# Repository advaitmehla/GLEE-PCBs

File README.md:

# GLEE-PCBs

This repository is for the schematics and PCBs I've worked on for Satlab.

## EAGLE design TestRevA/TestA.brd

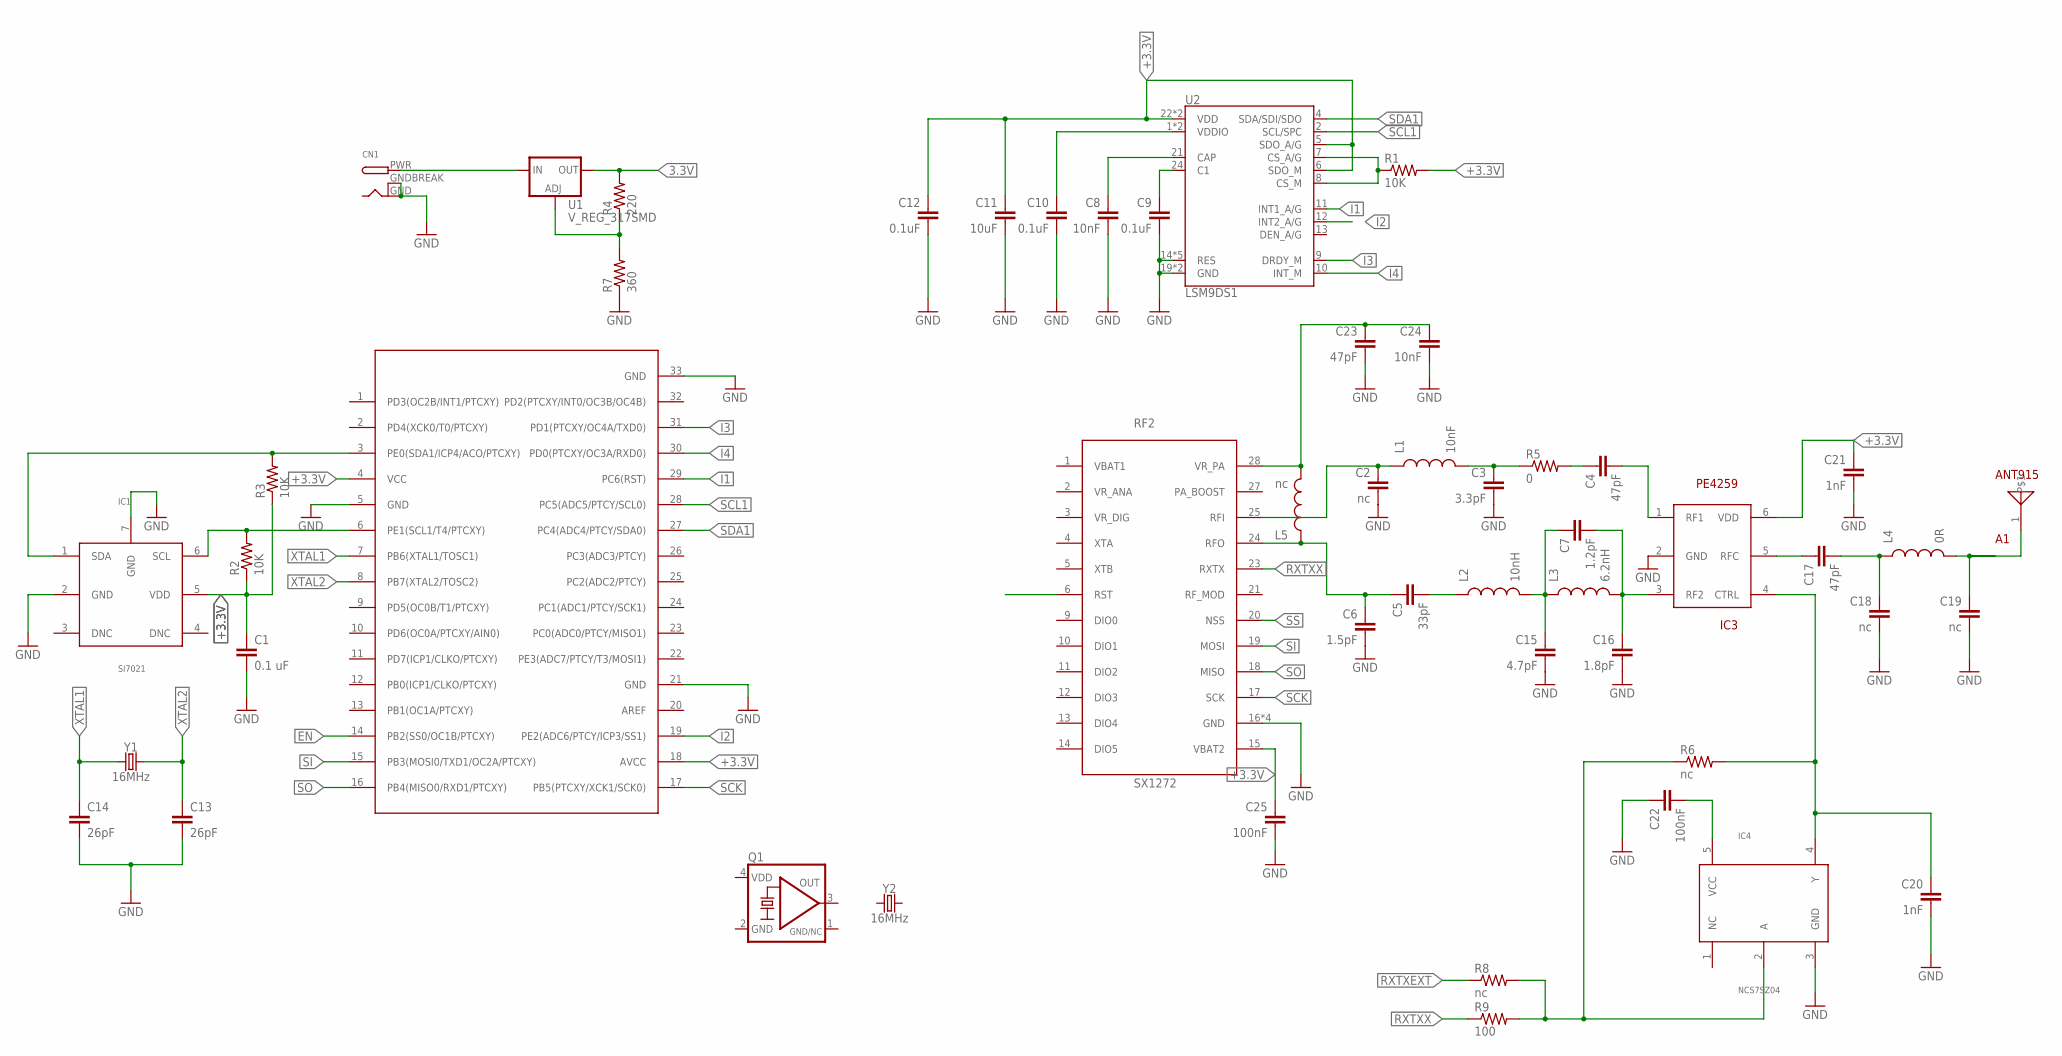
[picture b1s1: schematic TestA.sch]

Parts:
A1: ANT915
C1: 0.1 uF; 0603-CAP
C2, C18, C19: nc; 0603-CAP
C3: 3.3pF; 0603-CAP
C4, C17, C23: 47pF; 0603-CAP
C5: 33pF; 0603-CAP
C6: 1.5pF; 0603-CAP
C7: 1.2pF; 0603-CAP
C8, C24: 10nF; 0603-CAP
C9, C10, C12: 0.1uF; 0603-CAP
C11: 10uF; 0603-CAP
C13, C14: 26pF; 0603-CAP
C15: 4.7pF; 0603-CAP
C16: 1.8pF; 0603-CAP
C20, C21: 1nF; 0603-CAP
C22, C25: 100nF; 0603-CAP
CN1: DCBARRELPTH; DCJACK_2MM_PTH
IC1: SI7021
IC2: ATMEGA328-PB
IC3: PE4259
IC4: NCS7SZ04; NC7SZ04
L1: 10nF; 0603
L2: 10nH; 0603
L3: 6.2nH; 0603
L4: 0R; 0603
L5: nc; 0603
Q1: KXO-TCXO-CMOS-86; 2.5X2.0_KXO-86-TCXO
R1, R2, R3: 10K; 0603-RES
R4: 220; 0603-RES
R5: 0; 0603-RES
R6, R8: nc; 0603-RES
R7: 360; 0603-RES
R9: 100; 0603-RES
RF2: SX1272
U1: V_REG_317SMD; SOT223
U2: LSM9DS1; LGA24-8X4
Y1, Y2: 16MHz; CRYSTAL-SMD-2.0X1.6MM

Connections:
3.3V: R4.2, U1.2 (OUT)
+3.3V: C1.1, C11.1, C12.1, C21.1, C25.1, IC1.5 (VDD), IC2.4 (VCC), IC2.18 (AVCC), IC3.6 (VDD), R1.2, R2.1, R3.1, RF2.15 (VBAT2), U2.5 (SDO_A/G), U2.6 (SDO_M), U2.22 (VDD), U2.23 (VDD)
EN: IC2.14 (PB2(SS0/OC1B/PTCXY))
GND: C1.2, C2.2, C3.2, C6.2, C8.2, C9.2, C10.2, C11.2, C12.2, C13.2, C14.2, C15.2, C16.2, C18.2, C19.2, C20.2, C21.2, C22.1, C23.2, C24.2, C25.2, CN1.GND, CN1.GNDBREAK, IC1.2 (GND), IC1.7 (GND), IC2.5 (GND), IC2.21 (GND), IC2.33 (GND), IC3.2 (GND), IC4.3 (GND), Q1.2 (GND), R7.1, RF2.16 (GND), RF2.22 (GND), RF2.26 (GND), RF2.29 (GND), U2.14 (RES), U2.15 (RES), U2.16 (RES), U2.17 (RES), U2.18 (RES), U2.19 (GND), U2.20 (GND)
GND/NC: Q1.1 (GND/NC)
I1: IC2.29 (PC6(RST)), U2.11 (INT1_A/G)
I2: IC2.19 (PE2(ADC6/PTCY/ICP3/SS1)), U2.12 (INT2_A/G)
I3: IC2.31 (PD1(PTCXY/OC4A/TXD0)), U2.9 (DRDY_M)
I4: IC2.30 (PD0(PTCXY/OC3A/RXD0)), U2.10 (INT_M)
unnamed: C4.1, R5.2
unnamed: C23.1, C24.1, L5.2, RF2.28 (VR_PA)
unnamed: CN1.PWR, U1.3 (IN)
unnamed: C4.2, IC3.1 (RF1)
unnamed: R1.1, U2.7 (CS_A/G), U2.8 (CS_M)
unnamed: R4.1, R7.2, U1.1 (ADJ)
unnamed: C2.1, L1.1, RF2.25 (RFI)
unnamed: C8.1, U2.21 (CAP)
unnamed: C10.1, U2.1 (VDDIO), U2.3 (VDDIO)
unnamed: C3.1, L1.2, R5.1
unnamed: C5.1, C6.1, L5.1, RF2.24 (RFO)
unnamed: C7.1, C15.1, L2.2, L3.1
unnamed: C5.2, L2.1
unnamed: C7.2, C16.1, IC3.3 (RF2), L3.2
unnamed: A1.1, C19.1, L4.2
unnamed: C17.1, IC3.5 (RFC)
unnamed: C9.1, U2.24 (C1)
unnamed: C17.2, C18.1, L4.1
unnamed: C20.1, IC3.4 (CTRL), IC4.4 (Y), R6.2
unnamed: C22.2, IC4.5 (VCC)
unnamed: IC4.2 (A), R6.1, R8.2, R9.2
RXTXEXT: R8.1
RXTXX: R9.1, RF2.23 (RXTX)
SCK: IC2.17 (PB5(PTCXY/XCK1/SCK0)), RF2.17 (SCK)
SCL: IC1.6 (SCL), IC2.6 (PE1(SCL1/T4/PTCXY)), R2.2
SCL1: IC2.28 (PC5(ADC5/PTCY/SCL0)), U2.2 (SCL/SPC)
SDA: IC1.1 (SDA), IC2.3 (PE0(SDA1/ICP4/ACO/PTCXY)), R3.2
SDA1: IC2.27 (PC4(ADC4/PTCY/SDA0)), U2.4 (SDA/SDI/SDO)
SI: IC2.15 (PB3(MOSI0/TXD1/OC2A/PTCXY)), RF2.19 (MOSI)
SO: IC2.16 (PB4(MISO0/RXD1/PTCXY)), RF2.18 (MISO)
SS: RF2.20 (NSS)
VDD: Q1.4 (VDD)
XTAL1: C14.1, IC2.7 (PB6(XTAL1/TOSC1)), Y1.1
XTAL2: C13.1, IC2.8 (PB7(XTAL2/TOSC2)), Y1.3 (2)

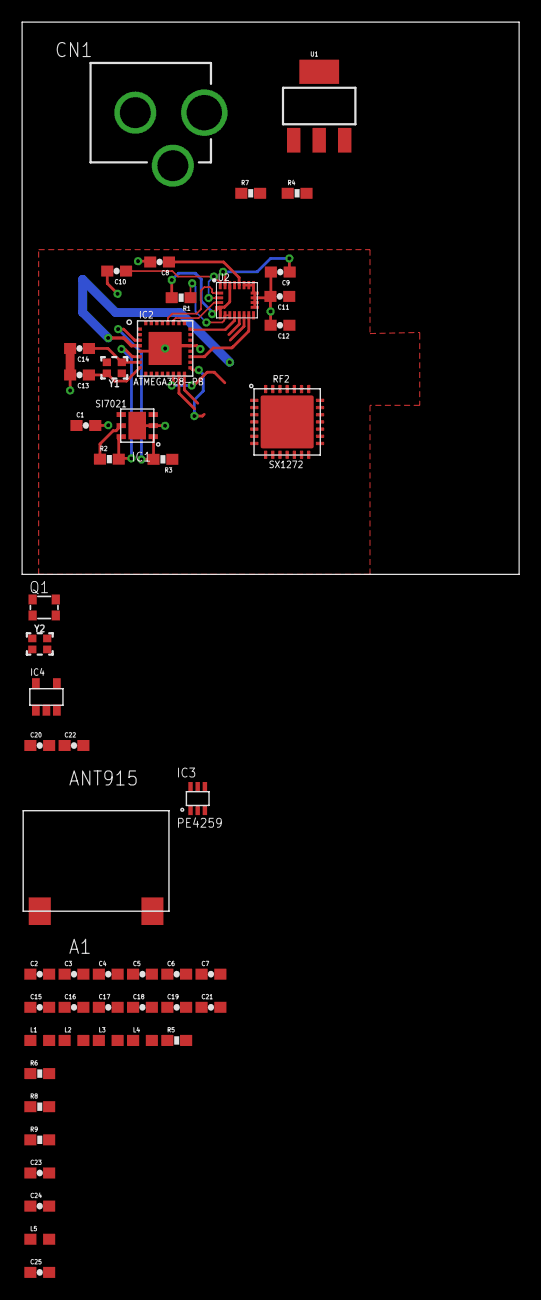
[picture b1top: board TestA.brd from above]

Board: 2 copper layers, 45.0 x 50.0 mm, 51 parts (0 on the bottom side), 38 nets.

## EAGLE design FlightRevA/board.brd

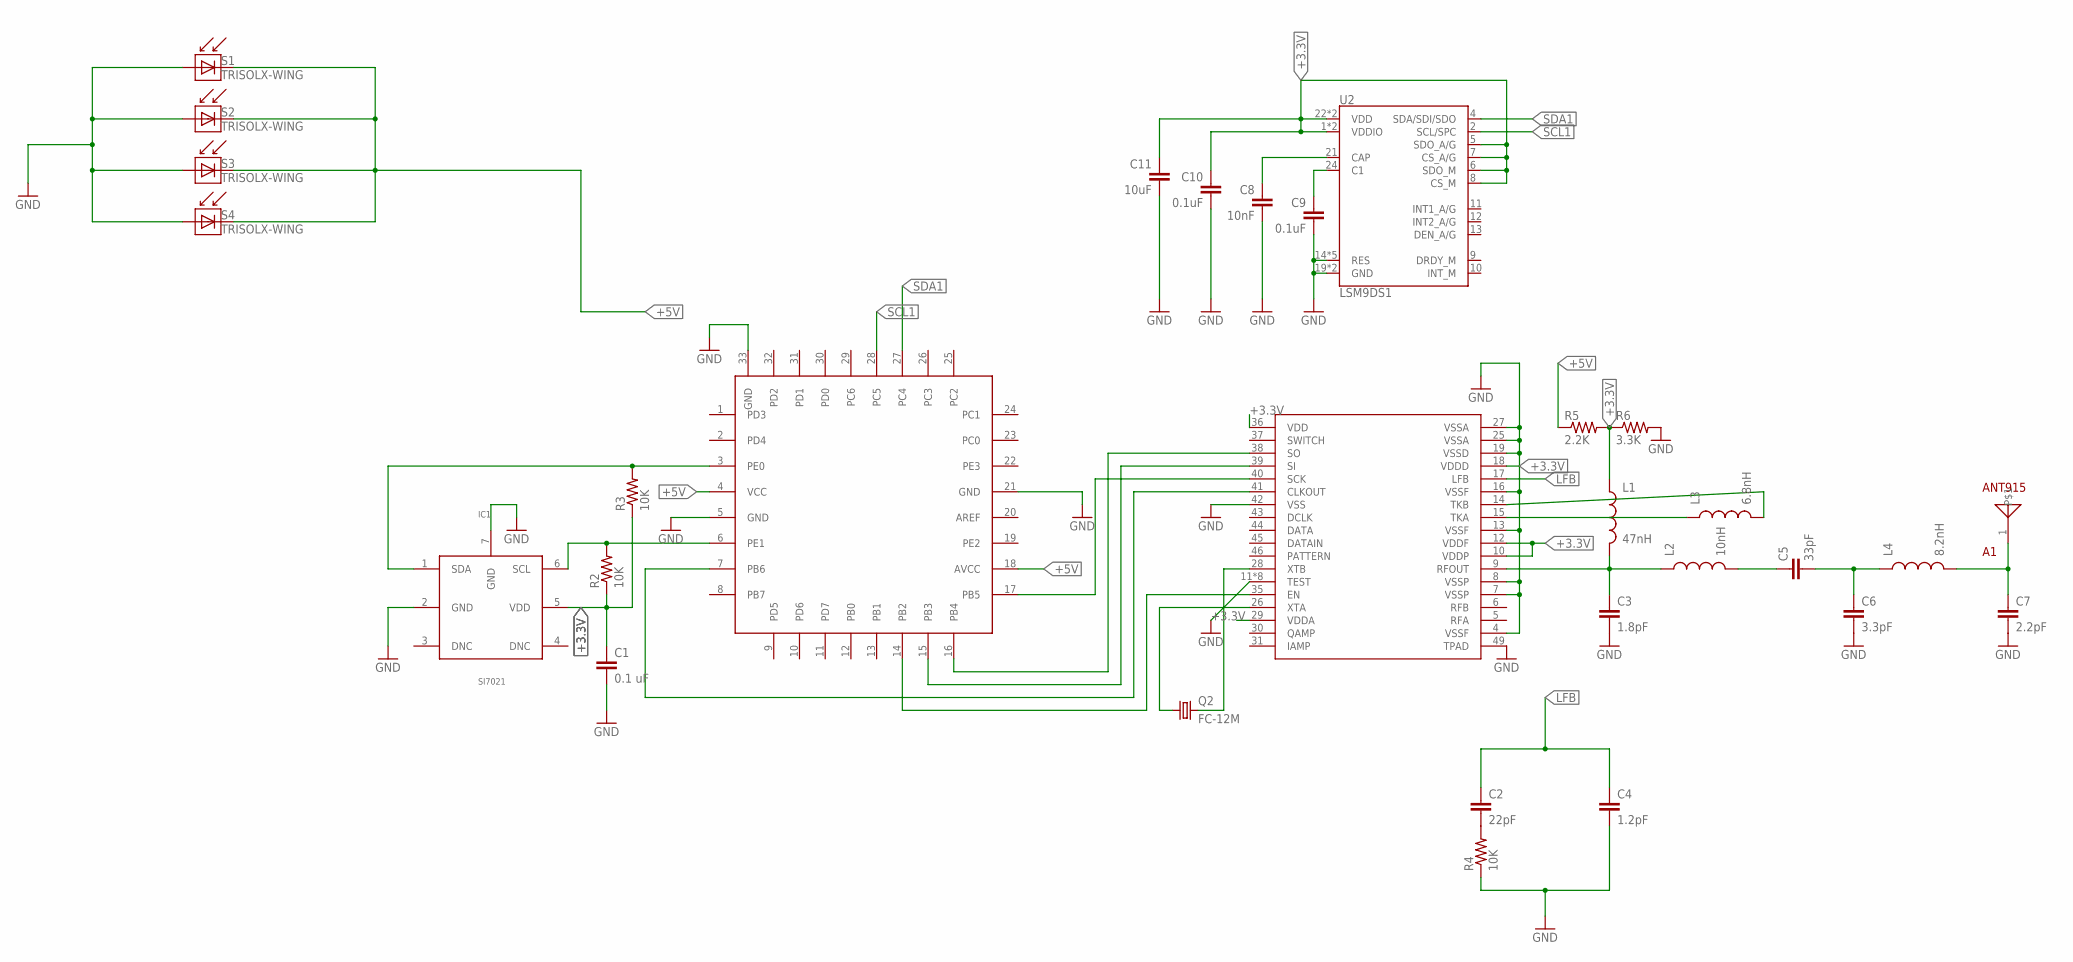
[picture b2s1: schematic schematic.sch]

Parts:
A1: ANT915
C1: 0.1 uF; 0603-CAP
C2: 22pF; 0603-CAP
C3: 1.8pF; 0603-CAP
C4: 1.2pF; 0603-CAP
C5: 33pF; 0603-CAP
C6: 3.3pF; 0603-CAP
C7: 2.2pF; 0603-CAP
C8: 10nF; 0603-CAP
C9, C10: 0.1uF; 0603-CAP
C11: 10uF; 0603-CAP
IC1: SI7021
IC2: ATMEGA328-PB
IC3: XE1203F
L1: 47nH; 0603
L2: 10nH; 0603
L3: 6.8nH; 0603
L4: 8.2nH; 0603
Q2: FC-12M
R2, R3, R4: 10K; 0603-RES
R5: 2.2K; 0603-RES
R6: 3.3K; 0603-RES
S1, S2, S3, S4: TRISOLX-WING; TRISOLX-T01
U2: LSM9DS1; LGA24-8X4

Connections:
+3.3V: C1.1, C10.1, C11.1, IC1.5 (VDD), IC3.10 (VDDP), IC3.12 (VDDF), IC3.18 (VDDD), IC3.29 (VDDA), IC3.36 (VDD), L1.1, R2.1, R3.1, R5.2, R6.1, U2.1 (VDDIO), U2.3 (VDDIO), U2.5 (SDO_A/G), U2.6 (SDO_M), U2.7 (CS_A/G), U2.8 (CS_M), U2.22 (VDD), U2.23 (VDD)
+5V: IC2.4 (VCC), IC2.18 (AVCC), R5.1, S1.P$2 (C), S2.P$2 (C), S3.P$2 (C), S4.P$2 (C)
GND: C1.2, C3.2, C4.2, C6.2, C7.2, C8.2, C9.2, C10.2, C11.2, IC1.2 (GND), IC1.7 (GND), IC2.5 (GND), IC2.21 (GND), IC2.33 (GND), IC3.4 (VSSF), IC3.7 (VSSP), IC3.8 (VSSP), IC3.11 (TEST), IC3.13 (VSSF), IC3.16 (VSSF), IC3.19 (VSSD), IC3.20 (TEST), IC3.21 (TEST), IC3.23 (TEST), IC3.24 (TEST), IC3.25 (VSSA), IC3.27 (VSSA), IC3.32 (TEST), IC3.33 (TEST), IC3.34 (TEST), IC3.42 (VSS), IC3.49 (TPAD), R4.1, R6.2, S1.P$3 (A), S2.P$3 (A), S3.P$3 (A), S4.P$3 (A), U2.14 (RES), U2.15 (RES), U2.16 (RES), U2.17 (RES), U2.18 (RES), U2.19 (GND), U2.20 (GND)
LFB: C2.1, C4.1, IC3.17 (LFB)
unnamed: C2.2, R4.2
unnamed: C3.1, IC3.9 (RFOUT), L1.2, L2.1
unnamed: IC2.7 (PB6), IC3.41 (CLKOUT)
unnamed: C5.1, L2.2
unnamed: IC2.14 (PB2), IC3.35 (EN)
unnamed: C5.2, C6.1, L4.1
unnamed: A1.1, C7.1, L4.2
unnamed: C8.1, U2.21 (CAP)
unnamed: IC3.15 (TKA), L3.1
unnamed: IC3.14 (TKB), L3.2
unnamed: IC3.26 (XTA), Q2.1
unnamed: IC3.28 (XTB), Q2.2
unnamed: IC2.15 (PB3), IC3.39 (SI)
unnamed: IC2.16 (PB4), IC3.38 (SO)
unnamed: IC2.17 (PB5), IC3.40 (SCK)
unnamed: C9.1, U2.24 (C1)
SCL: IC1.6 (SCL), IC2.6 (PE1), R2.2
SCL1: IC2.28 (PC5), U2.2 (SCL/SPC)
SDA: IC1.1 (SDA), IC2.3 (PE0), R3.2
SDA1: IC2.27 (PC4), U2.4 (SDA/SDI/SDO)

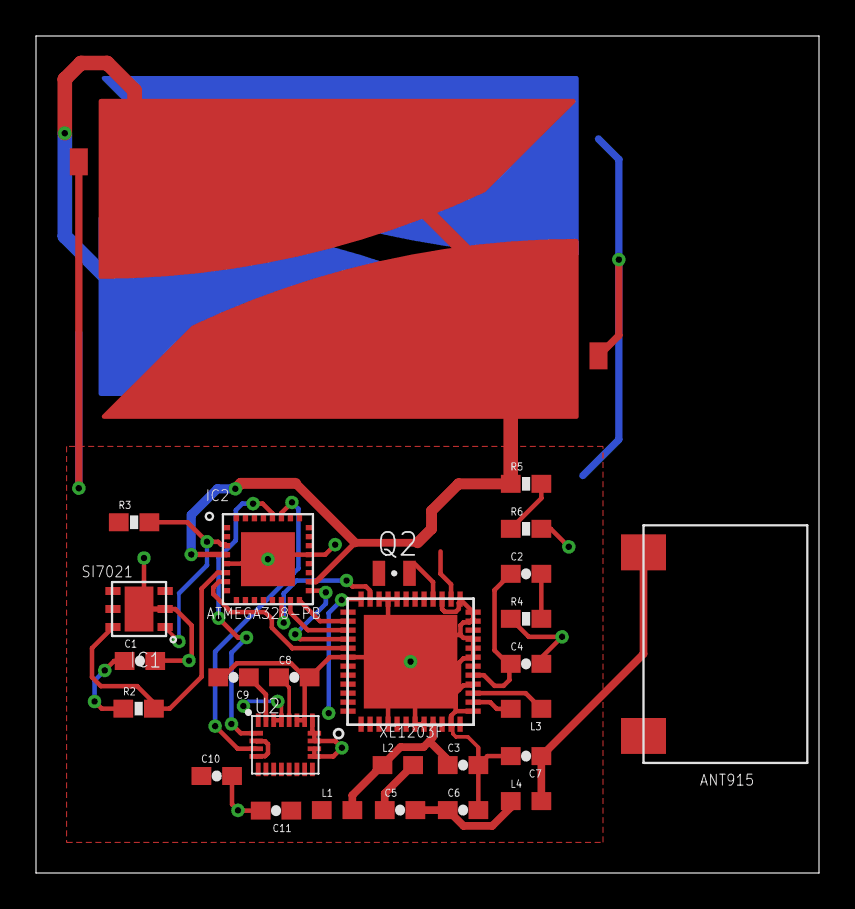
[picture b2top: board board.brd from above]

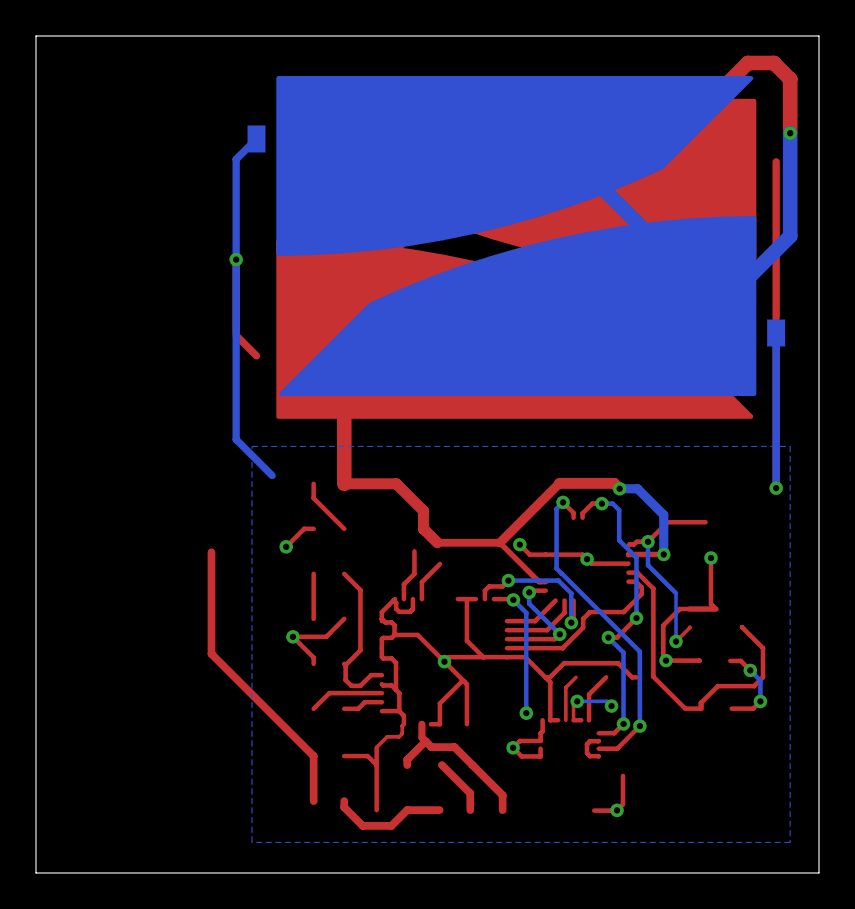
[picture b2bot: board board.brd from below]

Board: 2 copper layers, 43.5 x 46.5 mm, 30 parts (2 on the bottom side), 24 nets.

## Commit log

2021-08-28 Updated schematic of testing board, nearly done now
2021-09-03 Finished schematic
    Got rid of UHF inverter, changed all components to 0402 from 0603, made DIO connections.
2021-09-04 Completed board design, DRC and finishing touches remaining
2021-09-22 Completed first iteration

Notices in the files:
parts and their libraries:
SparkFun: Licensing: CC v3.0 Share-Alike You are welcome to use this library for commercial purposes.
SparkFun-Clocks: Licensing: Creative Commons ShareAlike 4.0 International - https://creativecommons.org/licenses/by-sa/4.0
crystal-geyer_V1_0: Copyright: Geyer-Electronic
